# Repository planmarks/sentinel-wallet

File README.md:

<div align="center">

# 🛡️ Sentinel Hardware Wallet

### Your keys and coins kept offline, signed offline, on a device you hold in your hand.

*A pocket-sized, open-source cold wallet for 14 blockchains.*

</div>

---

> ⚠️ **Status:** Firmware version `1.0.0`. This is a hobbyist / educational hardware-wallet project,
> not a certified secure product. Please read the [Security Model & Honest Limitations](#-security-model--honest-limitations)
> section before storing meaningful funds.

---

## 📖 What It Is

A cold wallet keeps the secret keys that control your crypto **offline**, away from any
internet-connected computer. Sentinel follows that model:

- **Keys are born on the device.** A BIP39 recovery phrase (12/18/24 words) is generated from the
  chip's hardware random number generator — or you can restore an existing phrase.
- **Keys stay on the device.** The seed is encrypted and written to the chip's flash. It only ever
  exists in plaintext in RAM while the wallet is unlocked, and it's wiped from RAM the moment you lock.
- **The device only signs what you approve.** The companion app builds a transaction and sends it
  over. Sentinel shows you the recipients and the fee on its own screen, and it won't sign until you
  press and hold the confirm button.
- **It works air-gapped.** USB and Bluetooth are just transports for passing transaction data back
  and forth; the signing itself is fully offline, and Bluetooth is **off by default**.

**Hardware target:** Seeed XIAO ESP32-C5 · Arduino-ESP32 core 3.3.5+
**Display:** SSD1306/SSD1315 128×64 I²C OLED
**Interface:** 6 buttons (Up / Down / OK / Back / Left / Right), USB serial, optional BLE

---

## 🪙 Supported Cryptocurrencies

Sentinel supports a wide range of chains across multiple cryptographic families. Like a real
hardware wallet, **EVM chains and tokens all sign through a single "Ethereum" engine**, and SPL /
TRC-20 tokens sign through their parent chain — so the list of *assets* you can hold is much larger
than the list of on-device menu entries.

### Bitcoin & UTXO chains

| Coin | Ticker | Curve | Derivation | Address type |
|------|--------|-------|------------|--------------|
| Bitcoin | BTC | secp256k1 | BIP84 `m/84'/0'` | Native SegWit (bech32) |
| Litecoin | LTC | secp256k1 | BIP84 `m/84'/2'` | Native SegWit (`ltc…`) |
| Dogecoin | DOGE | secp256k1 | BIP44 `m/44'/3'` | P2PKH |
| Dash | DASH | secp256k1 | BIP44 `m/44'/5'` | P2PKH |
| DigiByte | DGB | secp256k1 | BIP84 `m/84'/20'` | Native SegWit (`dgb…`) |
| Ravencoin | RVN | secp256k1 | BIP44 `m/44'/175'` | P2PKH |
| Bitcoin Cash | BCH | secp256k1 | `m/44'/145'` | CashAddr (SIGHASH_FORKID) |

Bitcoin (and other PSBT chains) support full **PSBT** signing with itemized output review.

### Ethereum & EVM chains

The **Ethereum** engine (`secp256k1`, BIP44 `m/44'/60'`, EIP-1559) signs for Ethereum **and every
EVM-compatible chain and ERC-20 token** the companion app knows about. The correct label is derived
from the transaction payload itself (chain ID for native transfers, contract address for tokens).

- **Ethereum (ETH)** and ERC-20 tokens such as **USDT** and **USDC**
- EVM chains routed through the same engine include:
  **BNB** Smart Chain, **Avalanche** (AVAX), **Polygon** (POL), **Base**, **Optimism** (OP),
  **Arbitrum** (ARB), **Cronos** (CRO), **Fantom** (FTM), **Ethereum Classic** (ETC), **Linea**,
  **Celo**, **Mantle** (MNT), **Flare** (FLR), **XDC**, **KuCoin Chain** (KCS), **X Layer** (OKB),
  **Filecoin EVM** (FILEVM), **BitTorrent Chain** (BTT), **IOTA EVM**, **Sonic** (S),
  **Kaia** (KAIA), **Hyperliquid** (HYPE), **Monad** (MON), and others (XTZ, XPL, M).

> New EVM chains and ERC-20 tokens generally need **no firmware change** — they're added on the app
> side, since they all share Ethereum's keys, addresses, and signing.

### Solana & SPL tokens

| Coin | Ticker | Curve | Derivation |
|------|--------|-------|------------|
| Solana | SOL | ed25519 | SLIP-0010 `m/44'/501'` |

Solana transfers are decoded and itemized for review; **SPL tokens** sign through the same Solana
engine.

### Cosmos ecosystem

All Cosmos-SDK chains use `secp256k1`, `m/44'/118'`, and bech32 addresses (differing only by prefix):

| Coin | Ticker | Address prefix |
|------|--------|----------------|
| Cosmos Hub | ATOM | `cosmos…` |
| dYdX | DYDX | `dydx…` |
| Axelar | AXL | `axelar…` |
| Babylon | BABY | `bbn…` |
| Celestia | TIA | `celestia…` |

### Other Layer-1 networks

| Coin | Ticker | Curve | Derivation | Notes |
|------|--------|-------|------------|-------|
| XRP Ledger | XRP | secp256k1 | `m/44'/144'` | base58check |
| Stellar | XLM | ed25519 | SLIP-0010 `m/44'/148'` | payments itemized |
| Cardano | ADA | BIP32-Ed25519 (Icarus) | `m/1852'/1815'` | Blake2b, staking support |
| Tron | TRX | secp256k1 | `m/44'/195'` | base58check (`T…`) |
| Tether on Tron | USDT (TRC-20) | secp256k1 | shares TRX address | |
| BitTorrent on Tron | BTT (TRC-20) | secp256k1 | shares TRX address | |
| Toncoin / Gram | TON | ed25519 | SLIP-10 `m/44'/607'` | v4R2 address |
| Polkadot | DOT | ed25519 | SLIP-10 `m/44'/354'` | SS58 address |
| Sui | SUI | ed25519 | SLIP-10 `m/44'/784'` | |
| Aptos | APT | ed25519 | SLIP-10 `m/44'/637'` | |
| NEAR Protocol | NEAR | ed25519 | SLIP-10 `m/44'/397'` | |
| Algorand | ALGO | ed25519 | SLIP-10 `m/44'/283'` | |
| Filecoin (native) | FIL | secp256k1 | `m/44'/461'` | `f1…` address |

> **Mainnet only.** This firmware deliberately does not support testnets.

---

## 🔒 Security Measures

Sentinel implements defense in depth across storage, key handling, transaction approval, and
connectivity.

### PIN & encrypted storage

- **PIN-gated unlock.** The device is locked at boot and requires a **4–8 digit PIN** to unlock.
- **Strong encryption at rest.** The seed (and optional passphrase) are stored with
  **AES-256-GCM** (authenticated encryption). The key is derived from your PIN using
  **PBKDF2-HMAC-SHA256 with 60,000 iterations** and a **random 16-byte salt** unique to each wallet.
  Each record also uses a random 12-byte IV, a 16-byte authentication tag, and associated data (AAD)
  binding — so tampered or corrupted ciphertext is rejected rather than mis-decrypted.
- **Anti-brute-force self-wipe.** After **5 wrong PIN attempts** the wallet **erases itself**.
  Crucially, the attempt counter is incremented **and persisted to flash *before* the PIN is
  checked**, so pulling power mid-attempt still "burns" the try — defeating power-cycle brute-force
  attacks.

### Key handling

- **Keys live in RAM only.** The decrypted seed exists in plaintext only while unlocked. On lock,
  auto-lock, or reset, all key material is **zeroized** (`mbedtls_platform_zeroize`), including
  temporary buffers, PIN buffers, and mnemonic strings after use.
- **Hardware RNG.** New seeds and cryptographic salts/IVs come from the ESP32-C5's hardware random
  number generator.
- **Optional BIP39 passphrase (25th word).** Adds a second secret on top of the seed, stored
  encrypted alongside it — enabling hidden-wallet style protection.
- **The recovery phrase is shown only on the OLED** — never printed to Serial or sent over BLE.
- **Auto-lock on inactivity.** After a configurable "Battery Saver" timeout, the device wipes keys
  from RAM, turns Bluetooth off, and returns to the PIN screen.

### Transaction safety

- **Offline signing.** Private keys never leave the device; the companion app never sees them. Only
  the *signed* transaction/PSBT is returned.
- **On-device review + hold-to-confirm.** Recipients and fees are shown on the device's own screen,
  and nothing is signed until you **press and hold** the confirm button. A compromised computer or
  app cannot make the device sign silently.
- **Blind-signing is off by default.** For chains whose transactions can't be fully decoded and
  itemized on-device, Sentinel **refuses to sign** unless you have explicitly enabled "Blind sign"
  for that specific coin in its settings — mirroring the blind-signing guard used by mainstream
  hardware wallets.

### Connectivity & privacy

- **Bluetooth is optional and off by default.** BLE is only a *transport* (a Nordic UART "serial
  over BLE" profile). The radio only comes up **after** the wallet is unlocked, a transaction sent
  over BLE **still** requires on-device confirmation, and BLE is torn down on lock.
- **No MAC-address tracking.** The device advertises a **random 16-bit ID** (generated once from the
  hardware RNG) instead of its factory Bluetooth MAC, so a passive scanner can't persistently track a
  specific physical unit.
- **Shoulder-surfing-resistant PIN pad.** The on-screen digit cursor starts on a **random** digit and
  jumps to a **new random** digit after each entry, so an onlooker can't infer digits by counting
  cursor movements. The PIN screen also dims when idle.

### Auditable, self-contained cryptography

All cryptographic primitives are vendored and run locally with **no network calls**:

- **TweetNaCl** — ed25519 signatures (Solana, Stellar, TON, DOT, Sui, Aptos, NEAR, Algorand)
- **SLIP-0010** — ed25519 hierarchical key derivation
- **BLAKE2b** — Cardano key derivation / hashing
- **uBitcoin** — secp256k1 keys, addresses, and PSBT signing
- **mbedTLS** — AES-256-GCM and PBKDF2 for storage encryption
- **qrcodegen** — offline QR code generation for receive addresses

---

## 🧭 How You Use It

1. **First boot:** create a **New Device** (generate a fresh recovery phrase) or **Restore** an
   existing 12/18/24-word phrase. Optionally add a passphrase. Set a PIN.
2. **Write down your recovery phrase** (shown only on the device screen) and store it safely offline.
3. **Receive:** pick a coin, view your address as text and a scannable **QR code**.
4. **Send:** the companion app builds a transaction and sends it over USB or BLE. Review the outputs
   and fee on the device, then **hold OK** to sign. The signed transaction goes back to the app to
   broadcast.
5. **Settings:** toggle Bluetooth, set the auto-lock timeout, change language, change PIN, per-coin
   blind-sign, uninstall coins, or reset the device.

---

## ⚖️ Security Model & Honest Limitations

To use this project responsibly, understand what it does **and doesn't** protect against:

- **No dedicated secure element.** The ESP32-C5 is a general-purpose microcontroller. Your keys are
  protected by **PIN-derived encryption + the 5-try self-wipe**, not by tamper-resistant secure-chip
  hardware. The strength of your protection therefore depends heavily on your **PIN choice** (and, for
  extra safety, a **passphrase**). A determined attacker with physical possession, lab equipment, and
  unlimited time is outside this design's threat model.
- **Blind signing carries risk.** Enabling blind-sign for a chain means you're trusting the
  transaction the app hands you, because the device can't fully decode it. Enable it only when you
  need it, and understand what you're approving.
- **You are your own backup.** There is no "forgot PIN" recovery. If you forget your PIN (self-wipe)
  or lose your device, **only your written recovery phrase can restore your funds.** Protect that
  phrase like the keys it is.
- **Hobbyist firmware.** This code has not undergone a formal third-party security audit. Review the
  source, and consider it experimental.

---

## 📂 Project Layout

- `coldwallet.ino` — main firmware: UI, menus, flows, command handling
- `config.h` — hardware pins, coin IDs, and derivation notes
- `store.cpp/.h` — encrypted NVS storage, PIN, self-wipe, settings
- `signer.cpp/.h` — PSBT loading, output review, signing
- `wallet.cpp/.h` — seed/entropy, BIP39, address derivation helpers
- `ble.cpp/.h` — optional Bluetooth (Nordic UART) transport
- Per-chain modules — `eth`, `sol`, `xlm`, `ada`, `xrp`, `cosmos`, `tron`, `ton`, `dot`, `sui`,
  `apt`, `near`, `algo`, `bch`, `fil`, `bnb`, etc.
- Vendored crypto — `tweetnacl`, `ed25519`, `slip10`, `blake2*`, `qrcodegen`

---

*Sentinel is provided as-is, for educational and personal use. Always verify addresses and
transaction details on the device screen before confirming.*

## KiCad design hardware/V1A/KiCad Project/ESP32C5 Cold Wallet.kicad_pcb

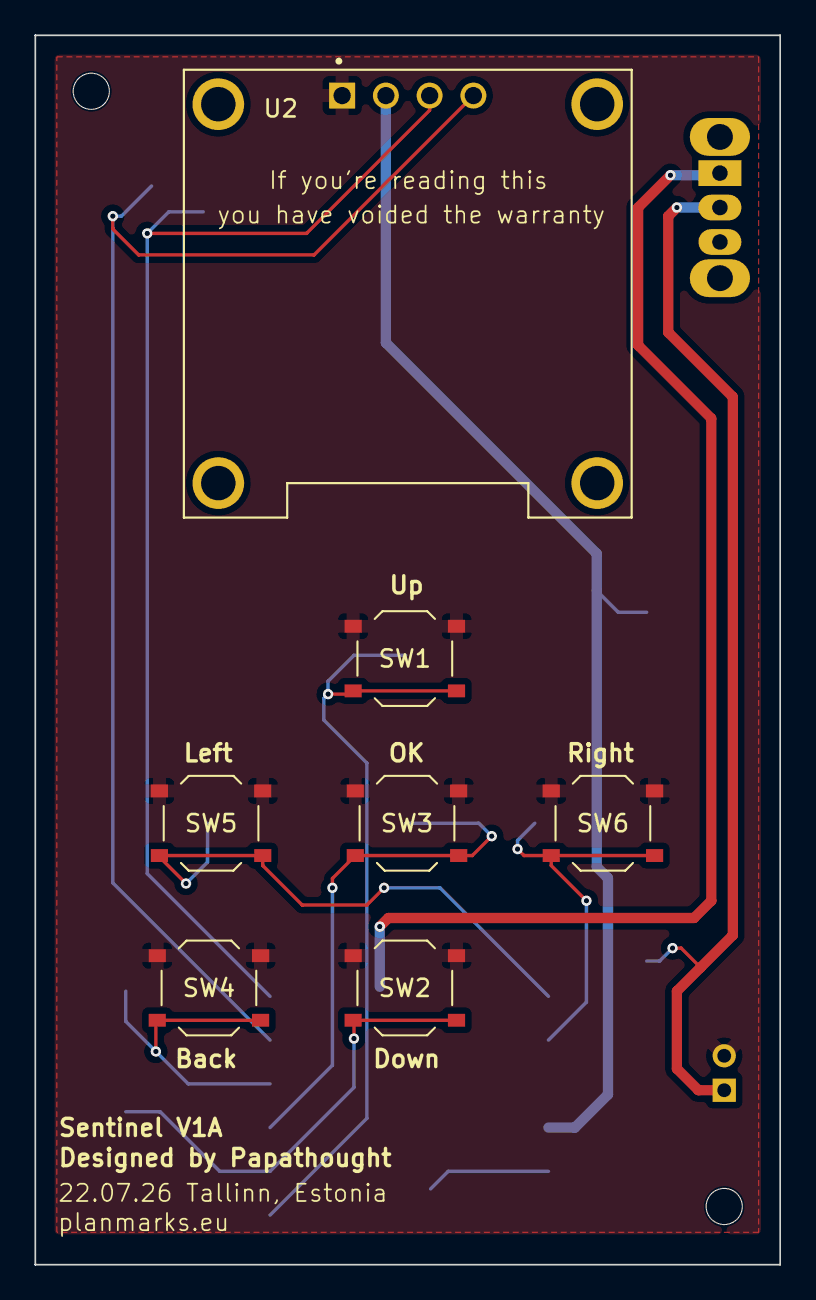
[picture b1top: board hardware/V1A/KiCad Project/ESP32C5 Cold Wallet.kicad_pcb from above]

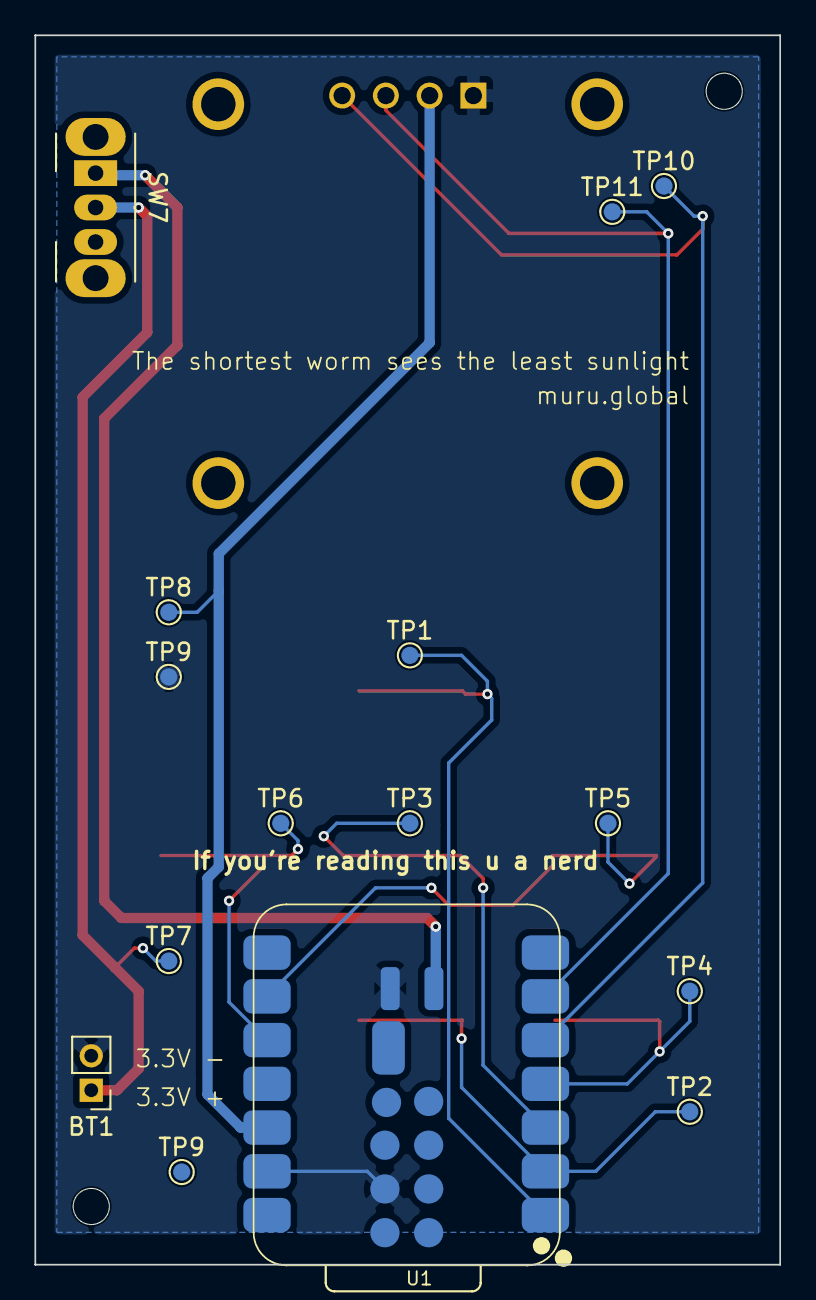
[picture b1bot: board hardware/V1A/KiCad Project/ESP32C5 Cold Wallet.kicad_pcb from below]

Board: 2 copper layers, 43.2 x 71.4 mm, 24 parts (15 on the bottom side), 12 nets.

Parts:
BT1: Battery; PinHeader_1x02_P2.00mm_Vertical
MNT: MountingHole_2.1mm
MNT#2: MountingHole_2.1mm
SW1: SW_Push UP; SW_Push_1P1T_XKB_TS-1187A
SW2: SW_Push DOWN; SW_Push_1P1T_XKB_TS-1187A
SW3: SW_Push OK; SW_Push_1P1T_XKB_TS-1187A
SW4: SW_Push BACK; SW_Push_1P1T_XKB_TS-1187A
SW5: SW_Push LEFT; SW_Push_1P1T_XKB_TS-1187A
SW6: SW_Push RIGHT; SW_Push_1P1T_XKB_TS-1187A
SW7: SW_SPDT; SW_Slide_SPDT_Angled_CK_OS102011MA1Q
TP1: SW-UP; TestPoint_Pad_D1.0mm
TP2: SW-DWN; TestPoint_Pad_D1.0mm
TP3: SW-OK; TestPoint_Pad_D1.0mm
TP4: SW-BCK; TestPoint_Pad_D1.0mm
TP5: SW-LFT; TestPoint_Pad_D1.0mm
TP6: SW-RHT; TestPoint_Pad_D1.0mm
TP7: BAT; TestPoint_Pad_D1.0mm
TP8: 3V3; TestPoint_Pad_D1.0mm
TP9, TP9#2: GND; TestPoint_Pad_D1.0mm
TP10: SDA; TestPoint_Pad_D1.0mm
TP11: SCL; TestPoint_Pad_D1.0mm
U1: XIAO-ESP32-C5-SMD
U2: DM-OLED096-636; MODULE_DM-OLED096-636

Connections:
+3.3V: TP8.1 (1_1), U1.12 (3V3_OUT), U2.2 (VCC_IN)
D0-SW1: SW1.2, TP1.1 (1_1), U1.1 (D0)
D1-SW2: SW2.2, TP2.1 (1_1), U1.2 (D1)
D2-SW3: SW3.2, TP3.1 (1_1), U1.3 (D2)
D3-SW4: SW4.2, TP4.1 (1_1), U1.4 (D3)
D4-SDA: TP10.1 (1_1), U1.5 (D4), U2.4 (SDA)
D5-SCL: TP11.1 (1_1), U1.6 (D5), U2.3 (SCL)
D8-SW5: SW5.2, TP5.1 (1_1), U1.9 (D8)
D9-SW6: SW6.2, TP6.1 (1_1), U1.10 (D9)
GND: BT1.2 (-), SW1.1, SW2.1, SW3.1, SW4.1, SW5.1, SW6.1, TP9#2.1 (1_1), U1.13 (GND), U1.18 (GND), U1.24 (GND), U2.1 (GND)
unnamed: BT1.1 (+), SW7.2 (B), TP7.1 (1_1)
VBAT: SW7.1 (A), U1.23 (VBAT)

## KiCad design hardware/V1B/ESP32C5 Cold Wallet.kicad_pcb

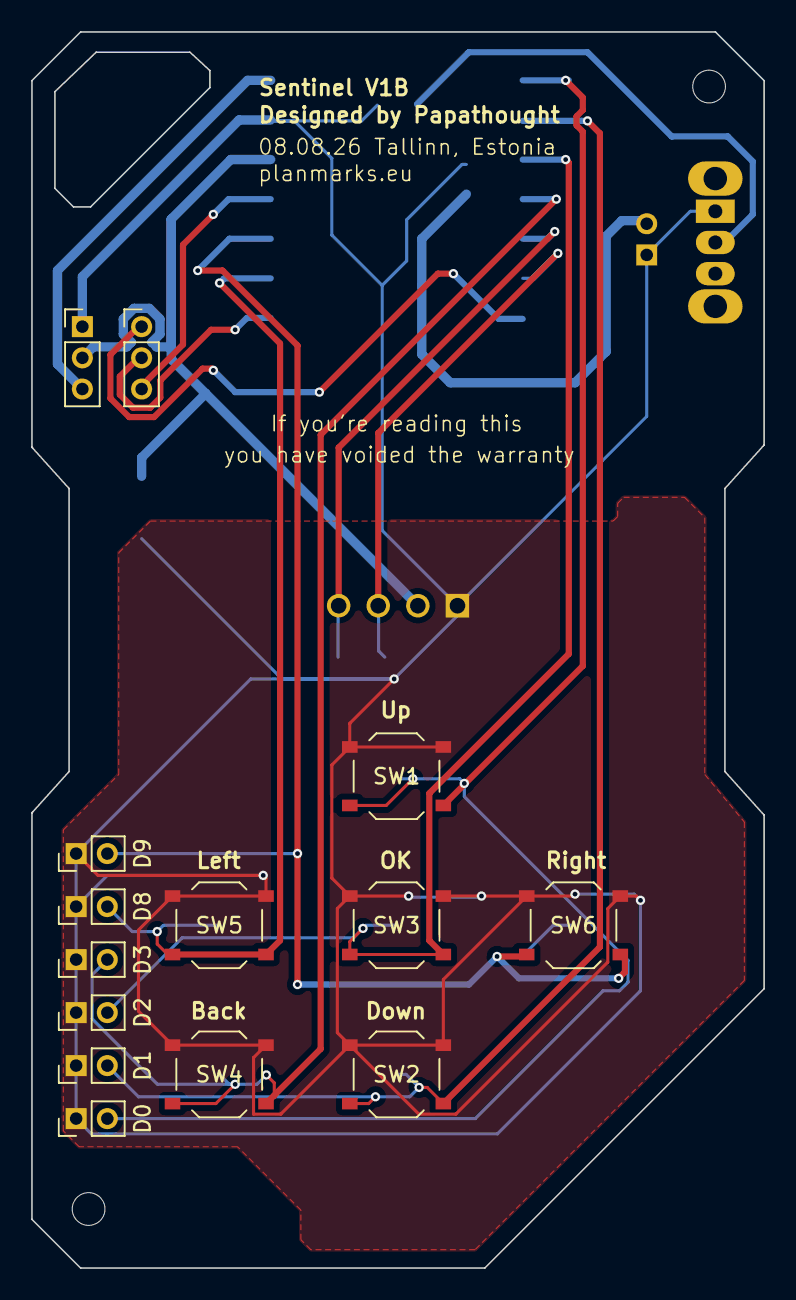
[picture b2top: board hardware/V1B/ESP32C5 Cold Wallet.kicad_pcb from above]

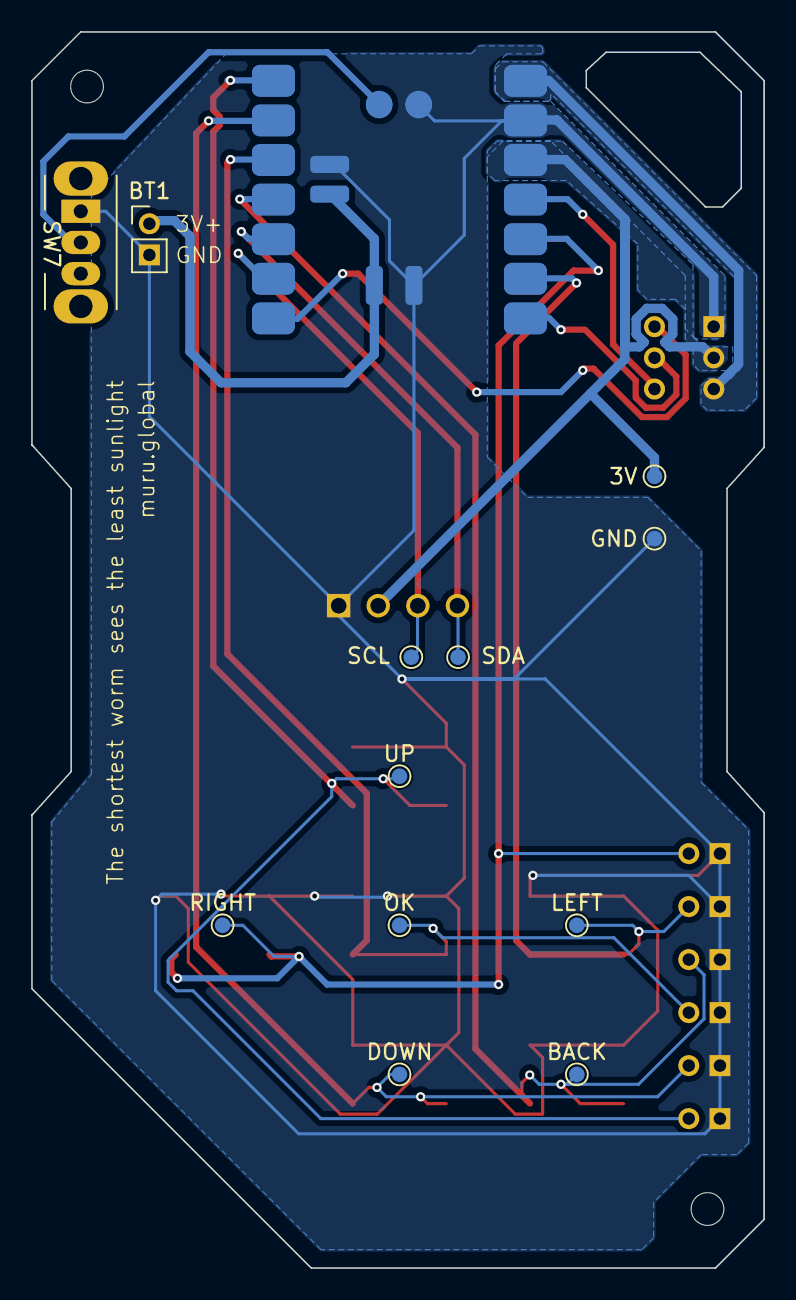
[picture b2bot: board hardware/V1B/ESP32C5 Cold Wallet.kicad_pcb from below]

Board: 2 copper layers, 47.0 x 79.3 mm, 29 parts (14 on the bottom side), 16 nets.

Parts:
3V: 3V3; TestPoint_Pad_D1.0mm
BACK: SW-BCK; TestPoint_Pad_D1.0mm
BT1: Battery; PinHeader_1x02_P2.00mm_Vertical
D0, D1, D2, D3, D8, D9: PinHeader_1x02_P2.00mm_Vertical
DOWN: SW-DWN; TestPoint_Pad_D1.0mm
GND: GND; TestPoint_Pad_D1.0mm
LEFT: SW-LFT; TestPoint_Pad_D1.0mm
MNT: MountingHole_2.1mm
MNT#2: MountingHole_2.1mm
OK: SW-OK; TestPoint_Pad_D1.0mm
RIGHT: SW-RHT; TestPoint_Pad_D1.0mm
SCL: SCL; TestPoint_Pad_D1.0mm
SDA: SDA; TestPoint_Pad_D1.0mm
SW1: SW_Push UP; SW_Push_1P1T_XKB_TS-1187A
SW2: SW_Push DOWN; SW_Push_1P1T_XKB_TS-1187A
SW3: SW_Push OK; SW_Push_1P1T_XKB_TS-1187A
SW4: SW_Push BACK; SW_Push_1P1T_XKB_TS-1187A
SW5: SW_Push LEFT; SW_Push_1P1T_XKB_TS-1187A
SW6: SW_Push RIGHT; SW_Push_1P1T_XKB_TS-1187A
SW7: SW_SPDT; SW_Slide_SPDT_Angled_CK_OS102011MA1Q
U1: XIAO-ESP32-C5-SMD
U2: DM-OLED096-636; MODULE_DM-OLED096-636
U3: XIAO-ESP32-C3-SMD
UP: SW-UP; TestPoint_Pad_D1.0mm

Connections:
+3.3V: 3V.1 (1_1), U1.12 (3V3_OUT), U2.2 (VCC_IN), U3.12 (3V3_OUT)
D0-SW1: D0.2, SW1.2, U1.1 (D0), U3.1 (D0), UP.1 (1_1)
D1-SW2: D1.2, DOWN.1 (1_1), SW2.2, U1.2 (D1), U3.2 (D1)
D2-SW3: D2.2, OK.1 (1_1), SW3.2, U1.3 (D2), U3.3 (D2)
D3-SW4: BACK.1 (1_1), D3.2, SW4.2, U1.4 (D3), U3.4 (D3)
D4-SDA: SDA.1 (1_1), U1.5 (D4), U2.4 (SDA), U3.5 (D4)
D5-SCL: SCL.1 (1_1), U1.6 (D5), U2.3 (SCL), U3.6 (D5)
D6: U1.7 (D6), U3.7 (D6)
D7: U1.8 (D7), U3.8 (D7)
D8-SW5: D8.2, LEFT.1 (1_1), SW5.2, U1.9 (D8), U3.9 (D8)
D9-SW6: D9.2, RIGHT.1 (1_1), SW6.2, U1.10 (D9), U3.10 (D9/BOOT)
D10: U1.11 (D10), U3.11 (D10)
EN: SW7.2 (B), U1.17 (EN), U3.17 (EN)
GND: BT1.2 (-), D0.1, D1.1, D2.1, D3.1, D8.1, D9.1, GND.1 (1_1), SW1.1, SW2.1, SW3.1, SW4.1, SW5.1, SW6.1, SW7.1 (A), U1.13 (GND), U1.18 (GND), U1.24 (GND), U2.1 (GND), U3.13 (GND), U3.18 (GND), U3.22 (GND)
VBAT: BT1.1 (+), U1.23 (VBAT), U3.21 (VBAT)
VBUS: U1.14 (VBUS), U3.14 (VBUS)
